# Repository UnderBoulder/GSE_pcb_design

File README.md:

# PCB_design
PCB design files for launch controllers

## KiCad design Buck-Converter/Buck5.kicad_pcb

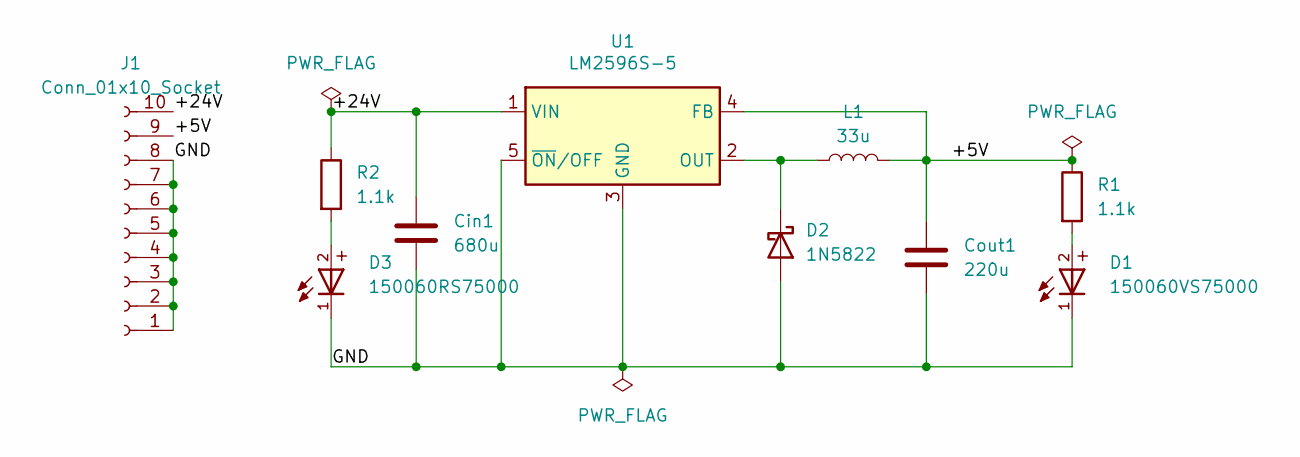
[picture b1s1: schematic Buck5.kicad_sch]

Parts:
Cin1: 680u; CAP_FT_G_PAN
Cout1: 220u; CAP_YX_8X11P5_RUB
D1: 150060VS75000; WL-SMCW_0603
D2: 1N5822; D_DO-201AD_P15.24mm_Horizontal
D3: 150060RS75000; WL-SMCW_0603
J1: Conn_01x10_Socket; PRECI-DIP_310-87-110-41-001101
L1: 33u; IND_DR127-330-R_EAT
R1, R2: 1.1k; RESC2012X65N
U1: LM2596S-5; TO-263-5_TabPin3

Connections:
/+5V: Cout1.1, J1.9, L1.2, R1.1, U1.4 (FB)
/+24V: Cin1.1, J1.10, R2.1, U1.1 (VIN)
/GND: Cin1.2, Cout1.2, D1.1, D2.2 (A), D3.1, J1.1, J1.2, J1.3, J1.4, J1.5, J1.6, J1.7, J1.8, U1.3 (GND), U1.5 (~ON/OFF)
unnamed: D1.2, R1.2
unnamed: D2.1 (K), L1.1, U1.2 (OUT)
unnamed: D3.2, R2.2

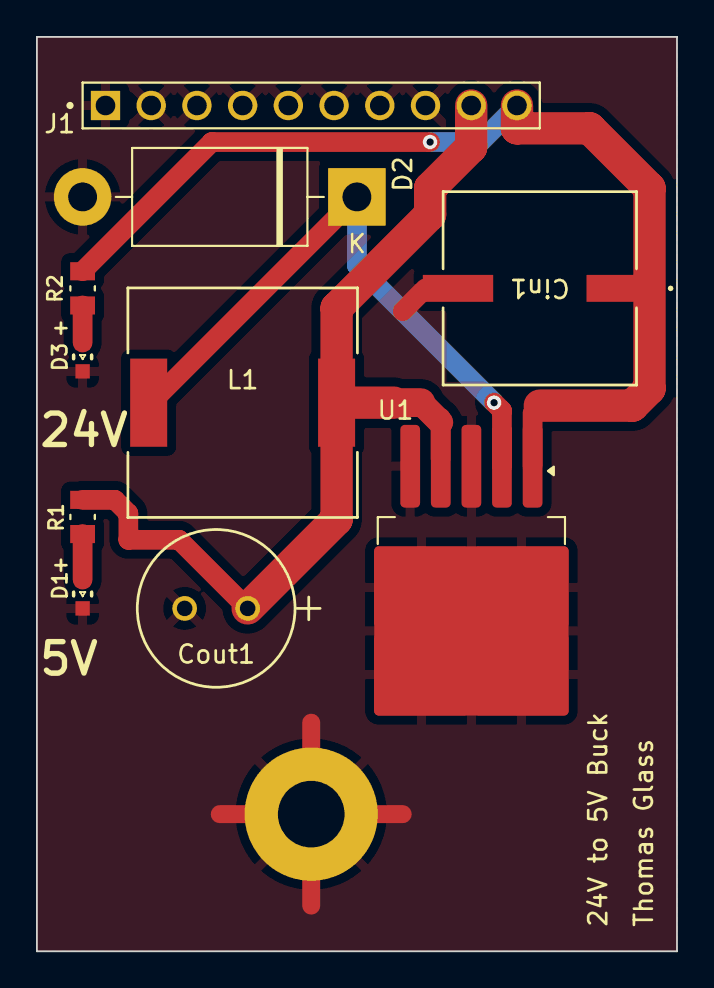
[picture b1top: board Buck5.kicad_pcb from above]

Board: 2 copper layers, 35.6 x 50.8 mm, 11 parts (0 on the bottom side), 6 nets.

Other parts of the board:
REF1: MountingHole_3.7mm_Pad

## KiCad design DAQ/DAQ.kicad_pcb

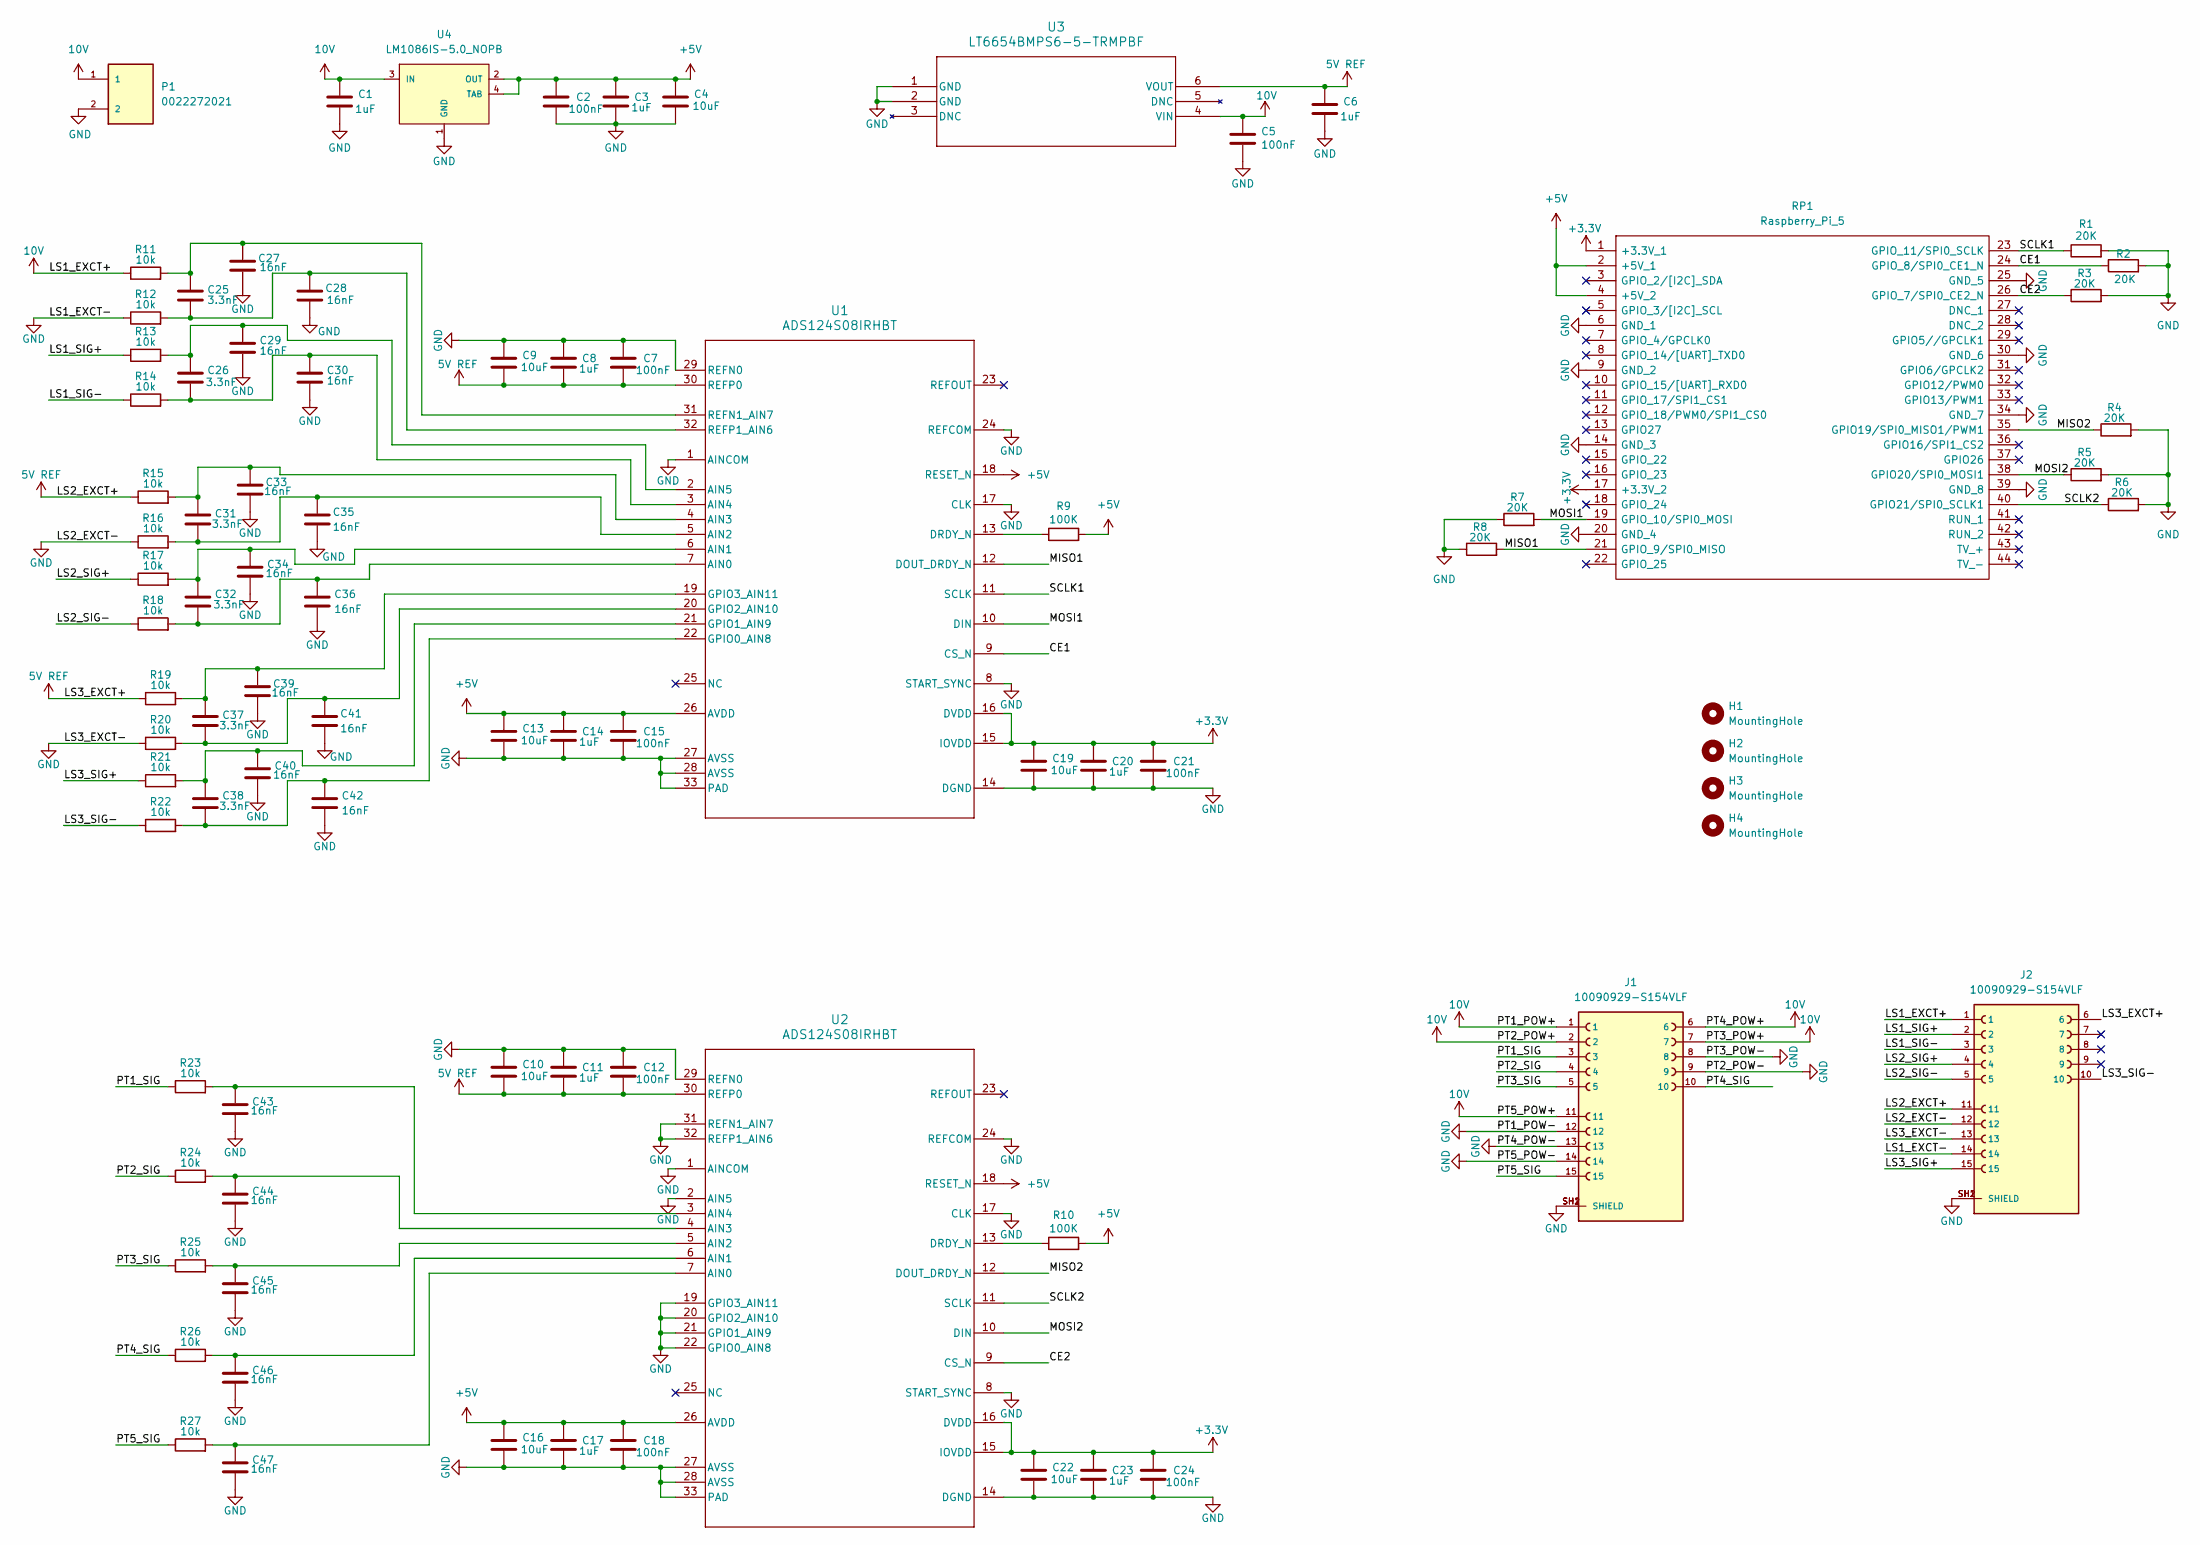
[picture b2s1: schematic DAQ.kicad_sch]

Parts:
C1, C3, C6, C8, C11, C14, C17, C20, C23: 1uF; CAPC1608X94N
C2, C5, C7, C12, C15, C18, C21, C24: 100nF; CAPC1608X97N
C4, C9, C10, C13, C16, C19, C22: 10uF; CAPC2012X145N
C25, C26, C31, C32, C37, C38: 3.3nF; CAP_CL10_SAM
C27, C28, C29, C30, C33, C34, C35, C36, C39, C40, C41, C42, C43, C44, C45, C46, C47: 16nF; CAPC3216X95N
H1, H2, H3, H4: MountingHole; MountingHole_2.5mm
J1, J2: 10090929-S154VLF; AMPHENOL_10090929-S154VLF; PARTREV H
P1: 0022272021; MOLEX_0022272021
R1, R2, R3, R4, R5, R6, R7, R8: 20K; RESC1508X50N
R9, R10: 100K; RESC1508X50N
R11, R12, R13, R14, R15, R16, R17, R18, R19, R20, R21, R22, R23, R24, R25, R26, R27: 10k; RC0603N_YAG-M
RP1: Raspberry_Pi_5; raspberrypi_2_3; Manufacturer_Part_Number Raspberry Pi 2 or 3
U1, U2: ADS124S08IRHBT; RHB0032M
U3: LT6654BMPS6-5-TRMPBF; TSOT-23_S6_LIT
U4: LM1086IS-5.0_NOPB; TO254P1524X483-4N

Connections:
5V REF: C6.1, C7.2, C8.2, C9.2, C10.2, C11.2, C12.2, J2.6, J2.11, R15.1, R19.1, U1.30 (REFP0), U2.30 (REFP0), U3.6 (VOUT)
10V: C1.1, C5.1, J1.1, J1.2, J1.6, J1.7, J1.11, J2.1, P1.1, R11.1, U3.4 (VIN), U4.3 (IN)
+3.3V: C19.1, C20.1, C21.1, C22.1, C23.1, C24.1, RP1.1 (+3.3V_1), RP1.17 (+3.3V_2), U1.15 (IOVDD), U1.16 (DVDD), U2.15 (IOVDD), U2.16 (DVDD)
+5V: C2.1, C3.1, C4.1, C13.1, C14.1, C15.1, C16.1, C17.1, C18.1, R9.2, R10.2, RP1.2 (+5V_1), RP1.4 (+5V_2), U1.18 (RESET_N), U1.26 (AVDD), U2.18 (RESET_N), U2.26 (AVDD), U4.2 (OUT), U4.4 (TAB)
/CE1: R2.1, RP1.24 (GPIO_8/SPI0_CE1_N), U1.9 (CS_N)
/CE2: R3.1, RP1.26 (GPIO_7/SPI0_CE2_N), U2.9 (CS_N)
/LS1_SIG+: J2.2, R13.1
/LS1_SIG-: J2.3, R14.1
/LS2_SIG+: J2.4, R17.1
/LS2_SIG-: J2.5, R18.1
/MISO1: R8.2, RP1.21 (GPIO_9/SPI0_MISO), U1.12 (DOUT_DRDY_N)
/MISO2: R4.1, RP1.35 (GPIO19/SPI0_MISO1/PWM1), U2.12 (DOUT_DRDY_N)
/MOSI1: R7.2, RP1.19 (GPIO_10/SPI0_MOSI), U1.10 (DIN)
/MOSI2: R5.1, RP1.38 (GPIO20/SPI0_MOSI1), U2.10 (DIN)
/PT1_SIG: J1.3, R23.1
/PT2_SIG: J1.4, R24.1
/PT3_SIG: J1.5, R25.1
/PT4_SIG: J1.10, R26.1
/PT5_SIG: J1.15, R27.1
/SCLK1: R1.1, RP1.23 (GPIO_11/SPI0_SCLK), U1.11 (SCLK)
/SCLK2: R6.1, RP1.40 (GPIO21/SPI0_SCLK1), U2.11 (SCLK)
GND: C1.2, C2.2, C3.2, C4.2, C5.2, C6.2, C7.1, C8.1, C9.1, C10.1, C11.1, C12.1, C13.2, C14.2, C15.2, C16.2, C17.2, C18.2, C19.2, C20.2, C21.2, C22.2, C23.2, C24.2, C27.2, C28.2, C29.2, C30.2, C33.2, C34.2, C35.2, C36.2, C39.2, C40.2, C41.2, C42.2, C43.2, C44.2, C45.2, C46.2, C47.2, J1.8, J1.9, J1.12, J1.13, J1.14, J1.SH1 (SHIELD), J1.SH2 (SHIELD), J2.12, J2.13, J2.14, J2.SH1 (SHIELD), J2.SH2 (SHIELD), P1.2, R1.2, R2.2, R3.2, R4.2, R5.2, R6.2, R7.1, R8.1, R12.1, R16.1, R20.1, RP1.6 (GND_1), RP1.9 (GND_2), RP1.14 (GND_3), RP1.20 (GND_4), RP1.25 (GND_5), RP1.30 (GND_6), RP1.34 (GND_7), RP1.39 (GND_8), U1.1 (AINCOM), U1.8 (START_SYNC), U1.14 (DGND), U1.17 (CLK), U1.24 (REFCOM), U1.27 (AVSS), U1.28 (AVSS), U1.29 (REFN0), U1.33 (PAD), U2.1 (AINCOM), U2.2 (AIN5), U2.8 (START_SYNC), U2.14 (DGND), U2.17 (CLK), U2.19 (GPIO3_AIN11), U2.20 (GPIO2_AIN10), U2.21 (GPIO1_AIN9), U2.22 (GPIO0_AIN8), U2.24 (REFCOM), U2.27 (AVSS), U2.28 (AVSS), U2.29 (REFN0), U2.31 (REFN1_AIN7), U2.32 (REFP1_AIN6), U2.33 (PAD), U3.1 (GND), U3.2 (GND), U4.1 (GND)
unnamed: C32.2, C36.1, R18.2, U1.7 (AIN0)
unnamed: C32.1, C34.1, R17.2, U1.6 (AIN1)
unnamed: C31.2, C35.1, R16.2, U1.5 (AIN2)
unnamed: C31.1, C33.1, R15.2, U1.4 (AIN3)
unnamed: C26.2, C30.1, R14.2, U1.3 (AIN4)
unnamed: C26.1, C29.1, R13.2, U1.2 (AIN5)
unnamed: R9.1, U1.13 (DRDY_N)
unnamed: C38.2, C42.1, R22.2, U1.22 (GPIO0_AIN8)
unnamed: C38.1, C40.1, R21.2, U1.21 (GPIO1_AIN9)
unnamed: C37.2, C41.1, R20.2, U1.20 (GPIO2_AIN10)
unnamed: C37.1, C39.1, R19.2, U1.19 (GPIO3_AIN11)
unnamed: C25.1, C27.1, R11.2, U1.31 (REFN1_AIN7)
unnamed: C25.2, C28.1, R12.2, U1.32 (REFP1_AIN6)
unnamed: C47.1, R27.2, U2.7 (AIN0)
unnamed: C46.1, R26.2, U2.6 (AIN1)
unnamed: C45.1, R25.2, U2.5 (AIN2)
unnamed: C44.1, R24.2, U2.4 (AIN3)
unnamed: C43.1, R23.2, U2.3 (AIN4)
unnamed: R10.1, U2.13 (DRDY_N)

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
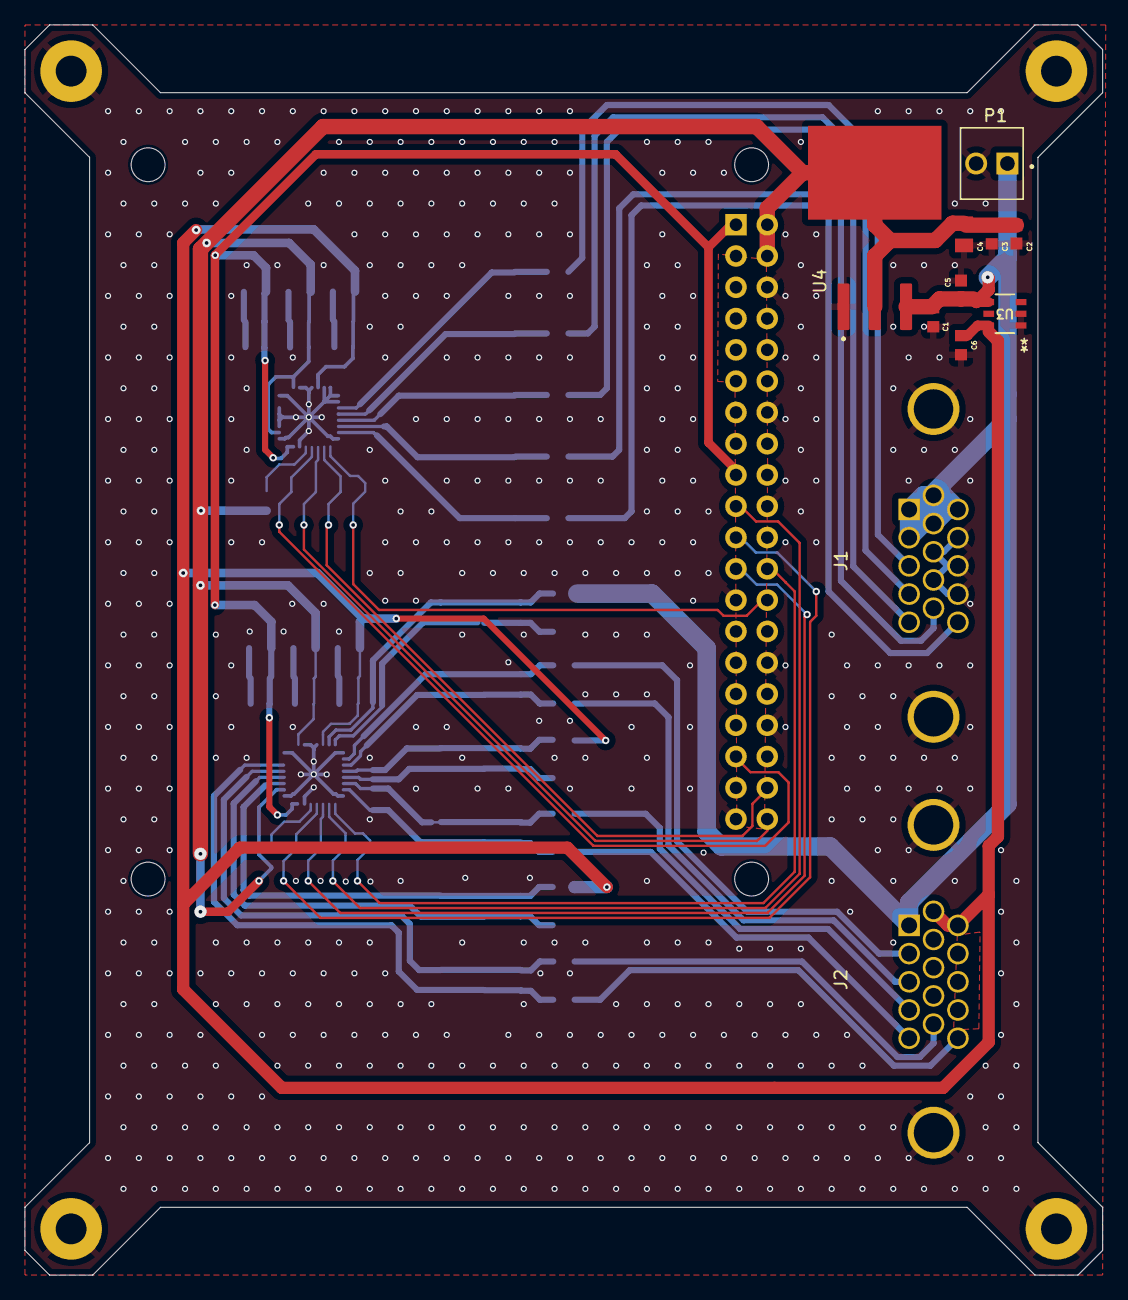
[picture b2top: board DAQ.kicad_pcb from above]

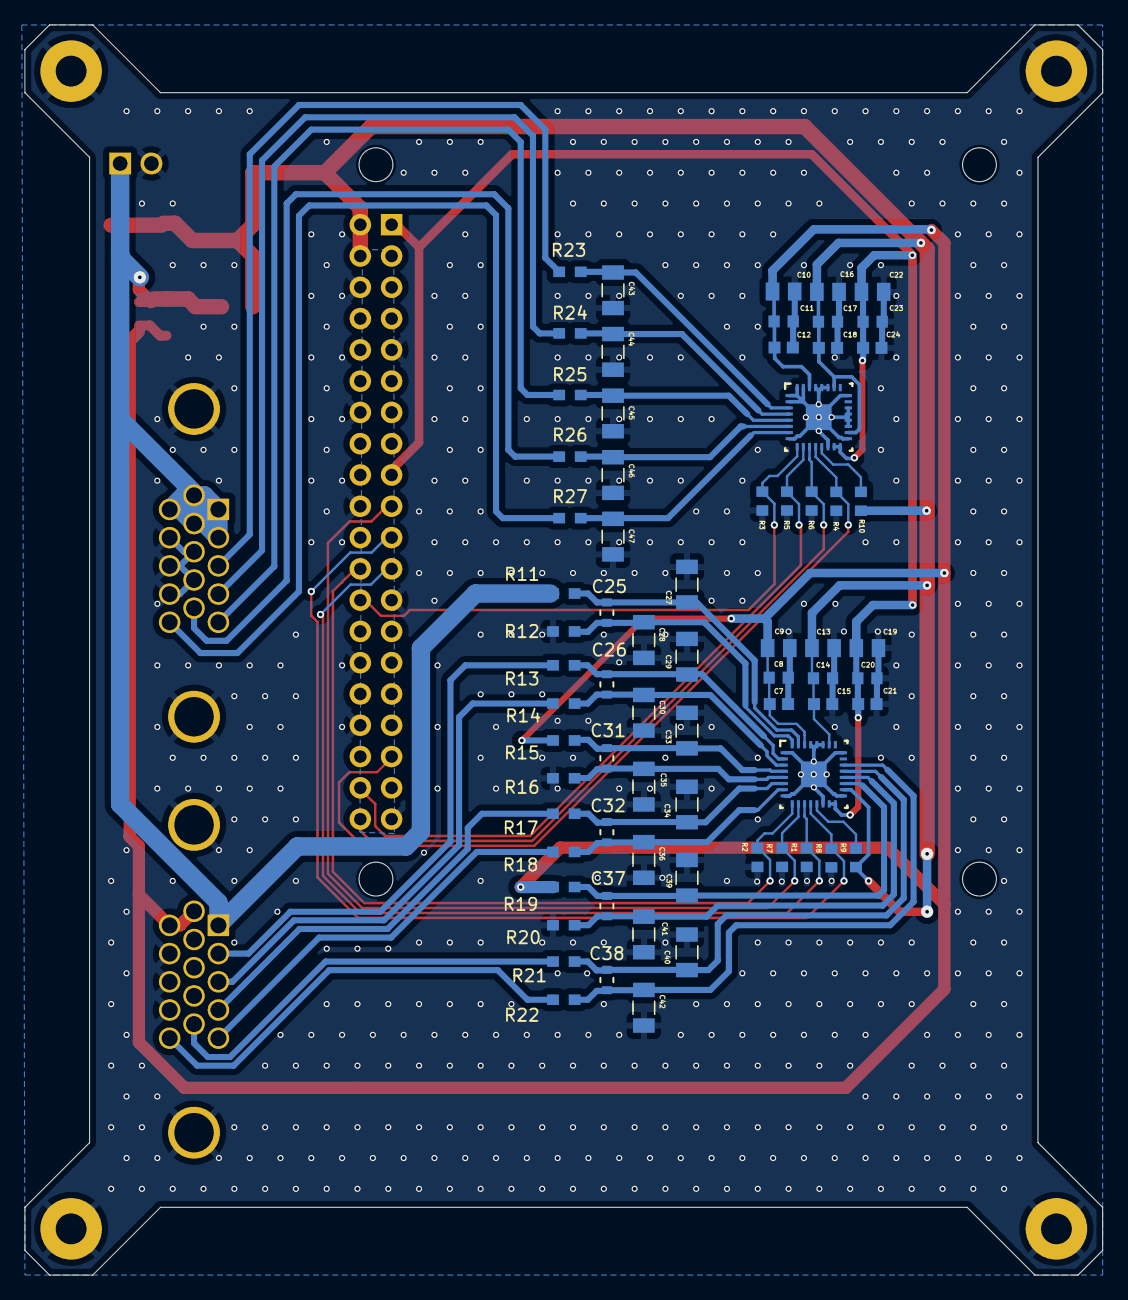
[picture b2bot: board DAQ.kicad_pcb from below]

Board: 2 copper layers, 87.5 x 101.5 mm, 82 parts (70 on the bottom side), 43 nets.

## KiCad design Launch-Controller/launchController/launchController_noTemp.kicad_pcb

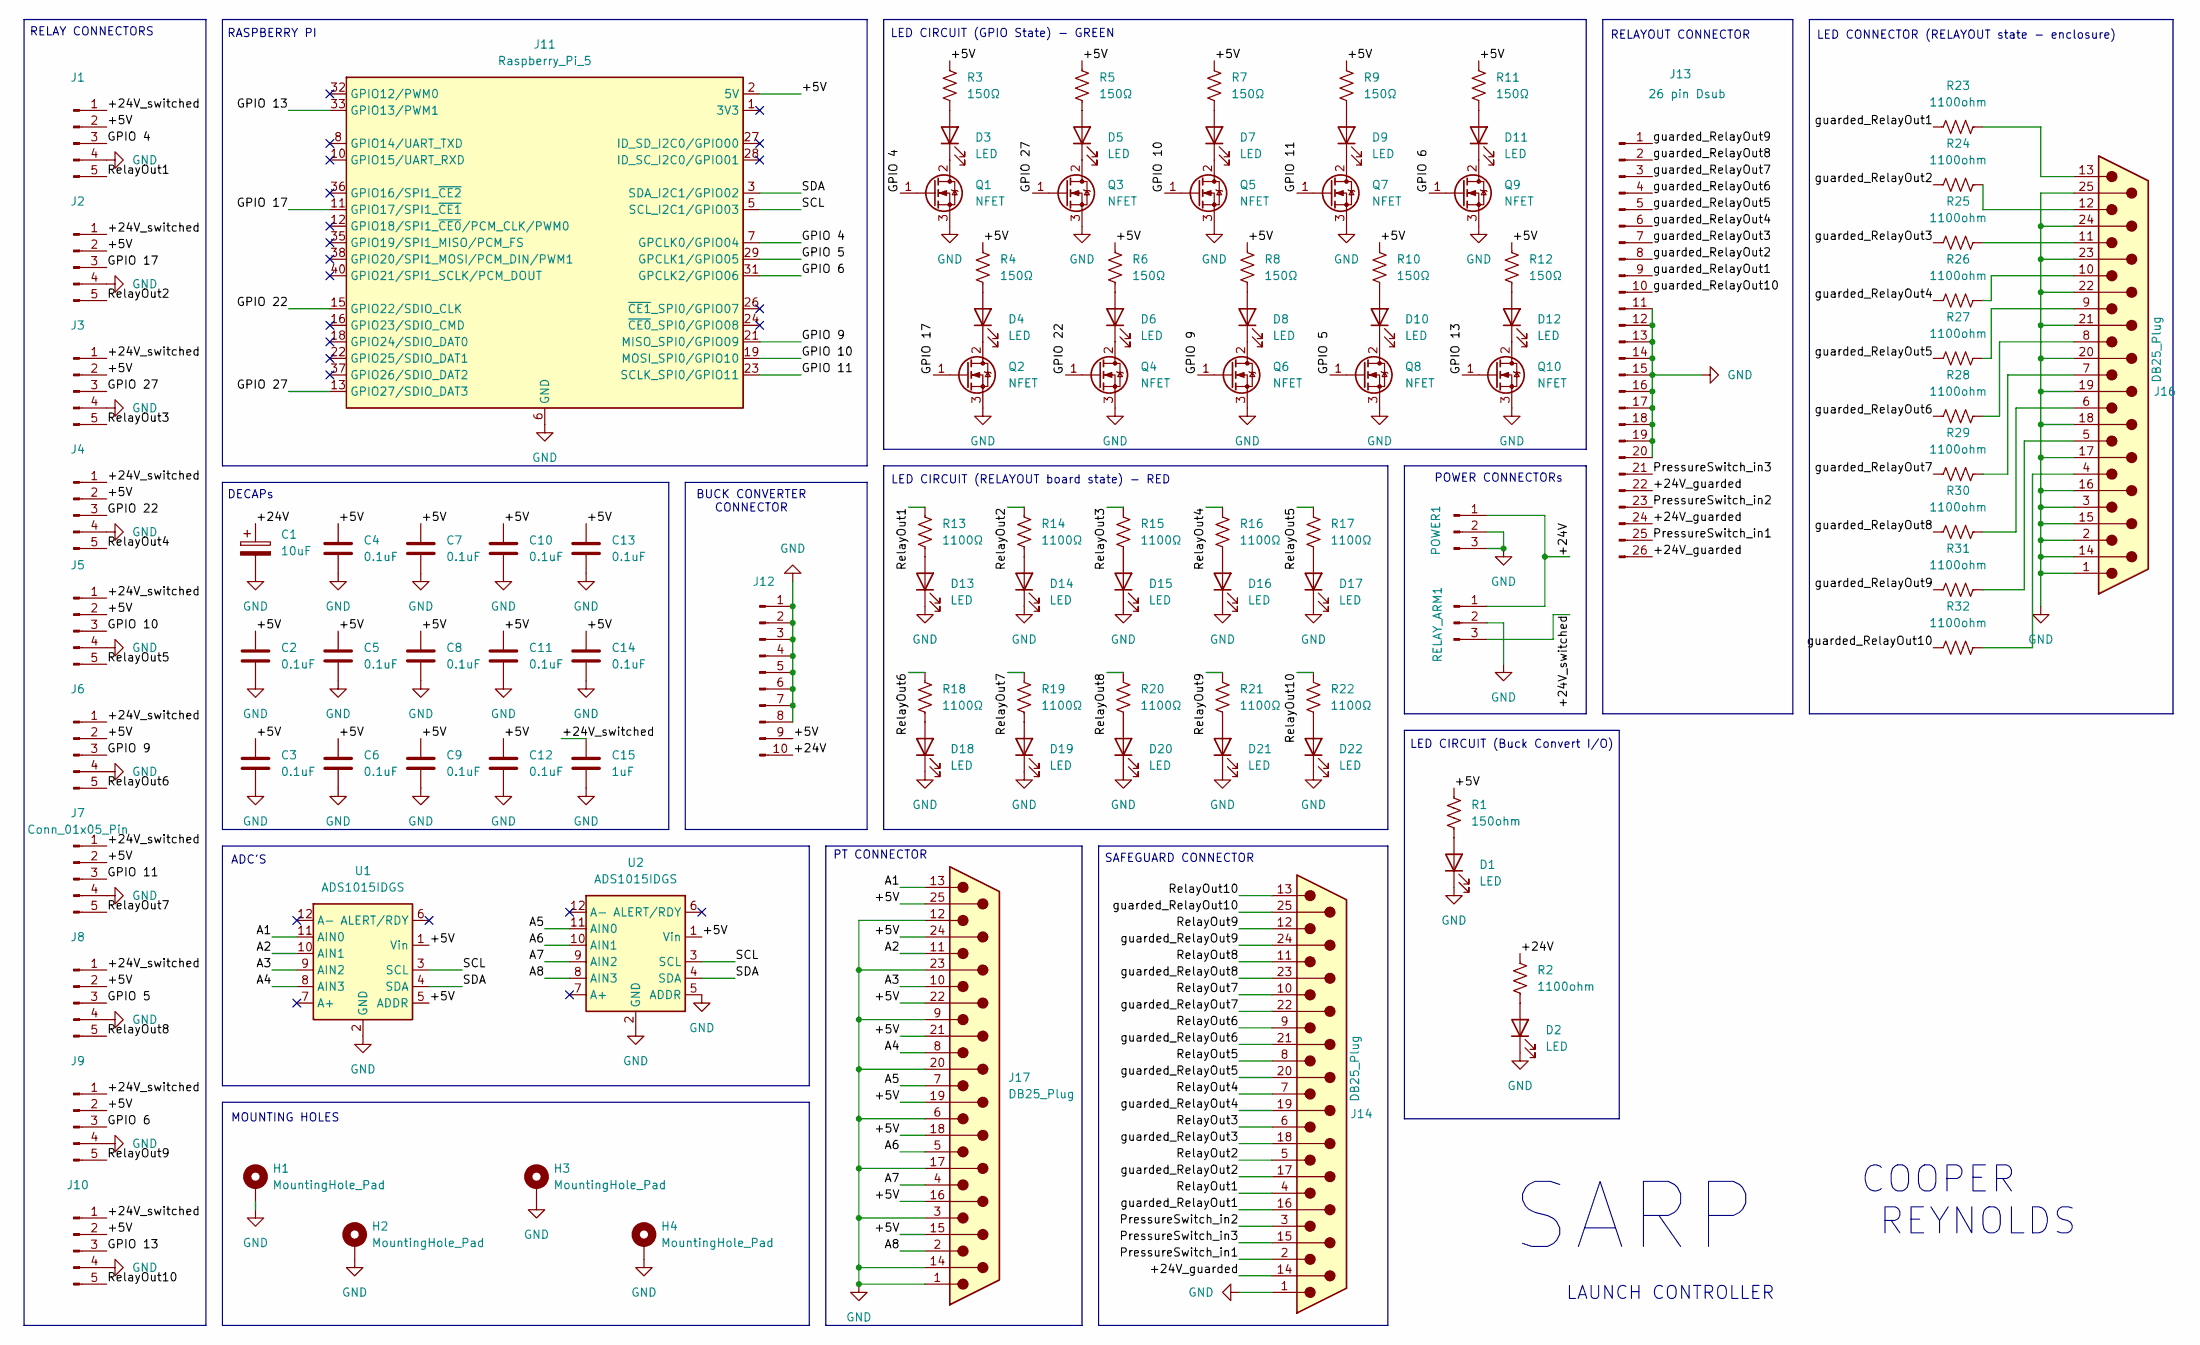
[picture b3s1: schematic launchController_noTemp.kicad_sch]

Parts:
C1: 10uF; CP_Radial_D6.3mm_P2.50mm
C2, C3, C4, C5, C6, C7, C8, C9, C10, C11, C12, C13, C14: 0.1uF; C_Disc_D5.1mm_W3.2mm_P5.00mm
C15: 1uF; C_Axial_L5.1mm_D3.1mm_P7.50mm_Horizontal
D1, D13, D14, D15, D16, D17, D18, D19, D20, D21, D22: LED; LED_D4.0mm
D2, D3, D4, D5, D6, D7, D8, D9, D10, D11, D12: LED; LED_D3.0mm
H1, H2, H3, H4: MountingHole_Pad; MountingHole_3.7mm_Pad
J1, J2, J3, J4, J5, J6, J7, J8, J9, J10: Conn_01x05_Pin; Relay Connector
J11: Raspberry_Pi_5; RPi_5_upside_down
J12: BuckConverter Connector
J13: 26 pin Dsub; DSUB-26-HD_Female_Horizontal_P2.29x1.98mm_EdgePinOffset8.35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
J14, J16, J17: DB25_Plug; DSUB-25_Female_Horizontal_P2.77x2.84mm_EdgePinOffset7.70mm_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
POWER1: Conn_01x03_Pin; 684M3W3203L461
Q1, Q2, Q3, Q4, Q5, Q6, Q7, Q8, Q9, Q10: NFET; TO-220-3_Horizontal_TabDown
R1: 150ohm; R_Axial_DIN0411_L9.9mm_D3.6mm_P12.70mm_Horizontal
R2, R23, R24, R25, R26, R27, R28, R29, R30, R31, R32: 1100ohm; R_Axial_DIN0207_L6.3mm_D2.5mm_P7.62mm_Horizontal
R3, R4, R5, R6, R7, R8, R9, R10, R11, R12: 150Ω; R_Axial_DIN0411_L9.9mm_D3.6mm_P12.70mm_Horizontal
R13, R14, R15, R16, R17, R18, R19, R20, R21, R22: 1100Ω; R_Axial_DIN0207_L6.3mm_D2.5mm_P7.62mm_Horizontal
RELAY_ARM1: Conn_01x03_Pin; 684M3W3203L461
U1, U2: ADS1015IDGS; ADS1015

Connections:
/+5V: C2.1, C3.1, C4.1, C5.1, C6.1, C7.1, C8.1, C9.1, C10.1, C11.1, C12.1, C13.1, C14.1, J1.2, J2.2, J3.2, J4.2, J5.2, J6.2, J7.2, J8.2, J9.2, J10.2, J11.2 (5V), J11.4 (5V), J12.9, J17.15, J17.16, J17.18, J17.19, J17.21, J17.22, J17.24, J17.25, R1.1, R3.1, R4.1, R5.1, R6.1, R7.1, R8.1, R9.1, R10.1, R11.1, R12.1, U1.1 (Vin), U1.5 (ADDR), U2.1 (Vin)
/+24V: C1.1, J12.10, POWER1.1, R2.1, RELAY_ARM1.1
/+24V_guarded: J13.22, J13.24, J13.26, J14.14
/+24V_switched: C15.1, J1.1, J2.1, J3.1, J4.1, J5.1, J6.1, J7.1, J8.1, J9.1, J10.1, RELAY_ARM1.3
/A1: J17.13, U1.11 (AIN0)
/A2: J17.11, U1.10 (AIN1)
/A3: J17.10, U1.9 (AIN2)
/A4: J17.8, U1.8 (AIN3)
/A5: J17.7, U2.11 (AIN0)
/A6: J17.5, U2.10 (AIN1)
/A7: J17.4, U2.9 (AIN2)
/A8: J17.2, U2.8 (AIN3)
/GPIO 4: J1.3, J11.7 (GPCLK0/GPIO04), Q1.1 (G)
/GPIO 5: J8.3, J11.29 (GPCLK1/GPIO05), Q8.1 (G)
/GPIO 6: J9.3, J11.31 (GPCLK2/GPIO06), Q9.1 (G)
/GPIO 9: J6.3, J11.21 (MISO_SPI0/GPIO09), Q6.1 (G)
/GPIO 10: J5.3, J11.19 (MOSI_SPI0/GPIO10), Q5.1 (G)
/GPIO 11: J7.3, J11.23 (SCLK_SPI0/GPIO11), Q7.1 (G)
/GPIO 13: J10.3, J11.33 (GPIO13/PWM1), Q10.1 (G)
/GPIO 17: J2.3, J11.11 (GPIO17/SPI1_~CE1), Q2.1 (G)
/GPIO 22: J4.3, J11.15 (GPIO22/SDIO_CLK), Q4.1 (G)
/GPIO 27: J3.3, J11.13 (GPIO27/SDIO_DAT3), Q3.1 (G)
/PressureSwitch_in1: J13.25, J14.2
/PressureSwitch_in2: J13.23, J14.3
/PressureSwitch_in3: J13.21, J14.15
/RelayOut1: J1.5, J14.4, R13.1
/RelayOut2: J2.5, J14.5, R14.1
/RelayOut3: J3.5, J14.6, R15.1
/RelayOut4: J4.5, J14.7, R16.1
/RelayOut5: J5.5, J14.8, R17.1
/RelayOut6: J6.5, J14.9, R18.1
/RelayOut7: J7.5, J14.10, R19.1
/RelayOut8: J8.5, J14.11, R20.1
/RelayOut9: J9.5, J14.12, R21.1
/RelayOut10: J10.5, J14.13, R22.1
/SCL: J11.5 (SCL_I2C1/GPIO03), U1.3 (SCL), U2.3 (SCL)
/SDA: J11.3 (SDA_I2C1/GPIO02), U1.4 (SDA), U2.4 (SDA)
/guarded_RelayOut1: J13.9, J14.16, R23.1
/guarded_RelayOut2: J13.8, J14.17, R24.1
/guarded_RelayOut3: J13.7, J14.18, R25.1
/guarded_RelayOut4: J13.6, J14.19, R26.1
/guarded_RelayOut5: J13.5, J14.20, R27.1
/guarded_RelayOut6: J13.4, J14.21, R28.1
/guarded_RelayOut7: J13.3, J14.22, R29.1
/guarded_RelayOut8: J13.2, J14.23, R30.1
/guarded_RelayOut9: J13.1, J14.24, R31.1
/guarded_RelayOut10: J13.10, J14.25, R32.1
GND: C1.2, C2.2, C3.2, C4.2, C5.2, C6.2, C7.2, C8.2, C9.2, C10.2, C11.2, C12.2, C13.2, C14.2, C15.2, D1.1 (K), D2.1 (K), D13.1 (K), D14.1 (K), D15.1 (K), D16.1 (K), D17.1 (K), D18.1 (K), D19.1 (K), D20.1 (K), D21.1 (K), D22.1 (K), H1.1, H2.1, H3.1, H4.1, J1.4, J2.4, J3.4, J4.4, J5.4, J6.4, J7.4, J8.4, J9.4, J10.4, J11.6 (GND), J11.9 (GND), J11.14 (GND), J11.20 (GND), J11.25 (GND), J11.30 (GND), J11.34 (GND), J11.39 (GND), J12.1, J12.2, J12.3, J12.4, J12.5, J12.6, J12.7, J12.8, J13.11, J13.12, J13.13, J13.14, J13.15, J13.16, J13.17, J13.18, J13.19, J13.20, J14.1, J16.1, J16.2, J16.3, J16.14, J16.15, J16.16, J16.17, J16.18, J16.19, J16.20, J16.21, J16.22, J16.23, J16.24, J16.25, J17.1, J17.3, J17.6, J17.9, J17.12, J17.14, J17.17, J17.20, J17.23, POWER1.2, POWER1.3, Q1.3 (S), Q2.3 (S), Q3.3 (S), Q4.3 (S), Q5.3 (S), Q6.3 (S), Q7.3 (S), Q8.3 (S), Q9.3 (S), Q10.3 (S), RELAY_ARM1.2, U1.2 (GND), U2.2 (GND), U2.5 (ADDR)
unnamed: D1.2 (A), R1.2
unnamed: D2.2 (A), R2.2
unnamed: D3.2 (A), R3.2
unnamed: D3.1 (K), Q1.2 (D)
unnamed: D4.2 (A), R4.2
unnamed: D4.1 (K), Q2.2 (D)
unnamed: D5.2 (A), R5.2
unnamed: D5.1 (K), Q3.2 (D)
unnamed: D6.2 (A), R6.2
unnamed: D6.1 (K), Q4.2 (D)
unnamed: D7.2 (A), R7.2
unnamed: D7.1 (K), Q5.2 (D)
unnamed: D8.2 (A), R8.2
unnamed: D8.1 (K), Q6.2 (D)
unnamed: D9.2 (A), R9.2
unnamed: D9.1 (K), Q7.2 (D)
unnamed: D10.2 (A), R10.2
unnamed: D10.1 (K), Q8.2 (D)
unnamed: D11.2 (A), R11.2
unnamed: D11.1 (K), Q9.2 (D)
unnamed: D12.2 (A), R12.2
unnamed: D12.1 (K), Q10.2 (D)
unnamed: D13.2 (A), R13.2
unnamed: D14.2 (A), R14.2
unnamed: D15.2 (A), R15.2
unnamed: D16.2 (A), R16.2
unnamed: D17.2 (A), R17.2
unnamed: D18.2 (A), R18.2
unnamed: D19.2 (A), R19.2
unnamed: D20.2 (A), R20.2
unnamed: D21.2 (A), R21.2
unnamed: D22.2 (A), R22.2
unnamed: J16.4, R32.2
unnamed: J16.5, R31.2
unnamed: J16.6, R30.2
unnamed: J16.7, R29.2
unnamed: J16.8, R28.2
unnamed: J16.9, R27.2
unnamed: J16.10, R26.2
unnamed: J16.11, R25.2
unnamed: J16.12, R24.2
unnamed: J16.13, R23.2

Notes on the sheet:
SAFEGUARD CONNECTOR
LED CONNECTOR (RELAYOUT state - enclosure)
LAUNCH CONTROLLER
LED CIRCUIT (Buck Convert I/O)
MOUNTING HOLES
RELAY CONNECTORS
LED CIRCUIT (GPIO State) - GREEN
POWER CONNECTORs
BUCK CONVERTER CONNECTOR
SARP
COOPER REYNOLDS
DECAPs
RELAYOUT CONNECTOR
RASPBERRY PI
LED CIRCUIT (RELAYOUT board state) - RED
ADC'S
PT CONNECTOR

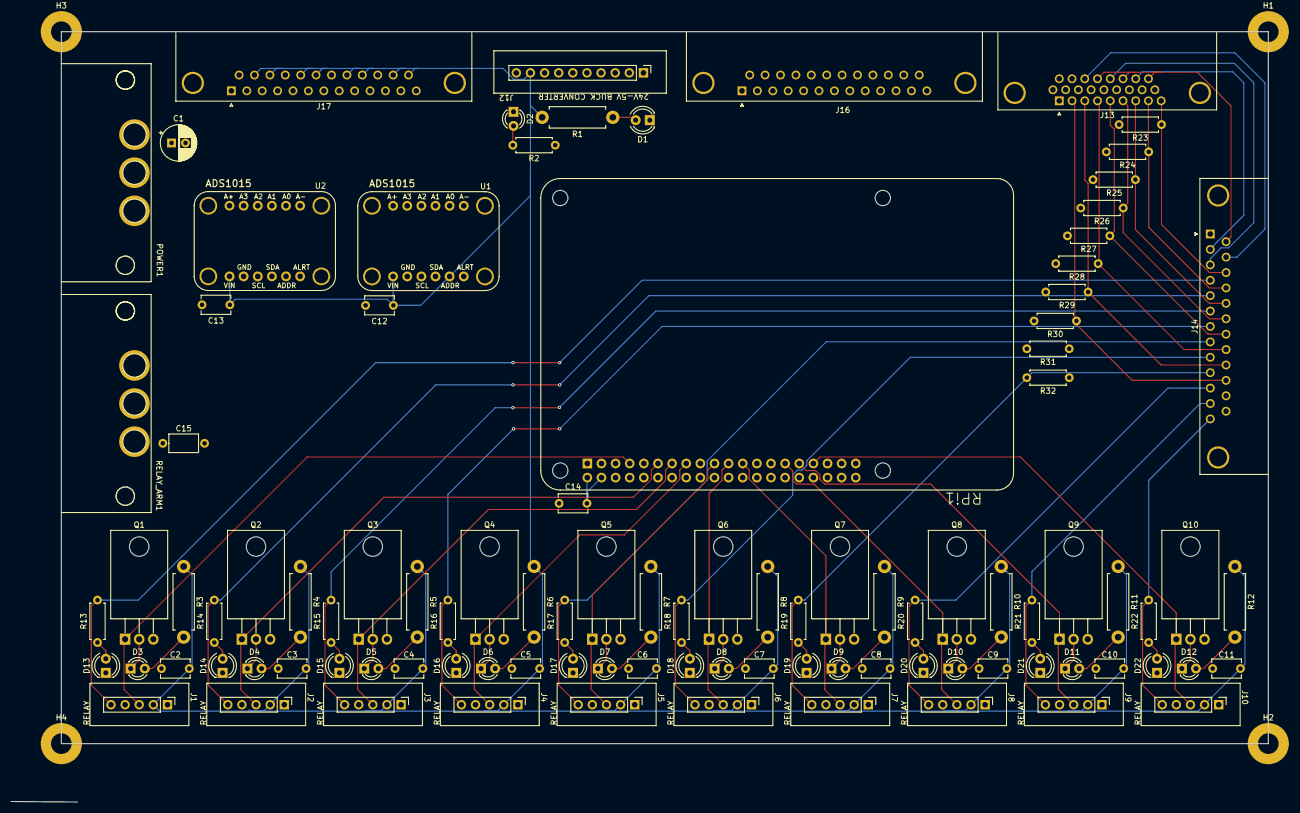
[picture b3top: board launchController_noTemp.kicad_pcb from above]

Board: 4 copper layers, 226.0 x 138.5 mm, 103 parts (0 on the bottom side), 90 nets.

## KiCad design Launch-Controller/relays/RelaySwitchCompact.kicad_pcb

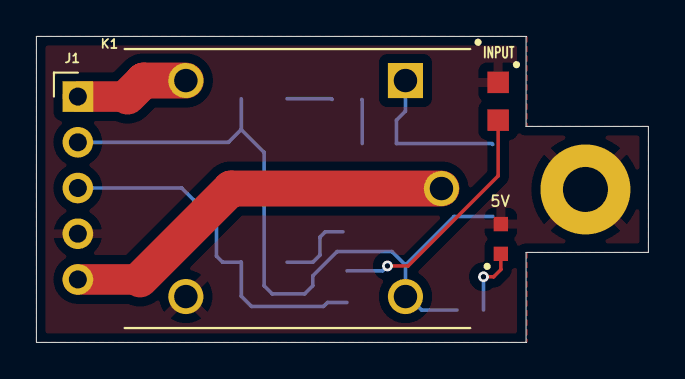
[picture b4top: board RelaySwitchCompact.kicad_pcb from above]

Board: 2 copper layers, 34.0 x 17.0 mm, 12 parts (0 on the bottom side), 10 nets.

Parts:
D1: RS1M-13-F; SMA_DIO-M
J1: Conn_01x05_Pin; PinHeader_1x05_P2.54mm_Vertical
K1: 1-1721150-0; RELAY_1-1721150-0
LED1: LED; LED_SML-D12V1WT86
LED2: HSMG-C170; LED_HSMS-C170
Mount: MountingHole_2.5mm_Pad
R1: 330R; RESC1607X60N
R2, R3: 100R; RESC1608X55N
R4: 10k; RESC1508X50N
U1: FOD817ASD; SOIC254P1016X385-4N
U2: FMMT634QTA; VREG_XC6206P282MR-G

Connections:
/+5V: D1.1, J1.2, K1.3, R1.2, U1.4
/GND: J1.4, K1.4, LED1.1 (K), LED2.C, Mount.1, R3.1, R4.1, U2.3 (E)
/GPIO: J1.3, R4.2, U1.1
/RelayIn: J1.1, K1.5
/RelayOut: J1.5, K1.2
unnamed: LED1.2 (A), R1.1
unnamed: R2.1, U1.3
unnamed: R3.2, U1.2
unnamed: R2.2, U2.2 (B)
unnamed: D1.2, K1.1, U2.1 (C)

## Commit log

2025-02-18 Fixing github repo
2025-02-19 added buck converter files

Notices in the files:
parts and their libraries:
COPYRIGHT: Copyright (C) 2023 Ultra Librarian. All rights reserved.
